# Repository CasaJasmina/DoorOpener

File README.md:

# Door Opener
A combination of a capacitive keypad/doorbell and a hacked lockitron.
At the moment there is a wired connection between the two parts of the project allowing the opening of the door when the right combination is pressed.

## The keypad

The keypad is based on Arduino YUN.
It uses MPR1221 for capacitive touch detection and addressable RGB led to provide feedbacks to the user.
find more inside the keypad folder

## The lockitron

To open the door a old model of lockitron was hacked. You can get the mechanical parts from Adafruit.
A custom PCB based on ESP8266 was designed and milled.

## TODO
- connect the system to Arduino Cloud

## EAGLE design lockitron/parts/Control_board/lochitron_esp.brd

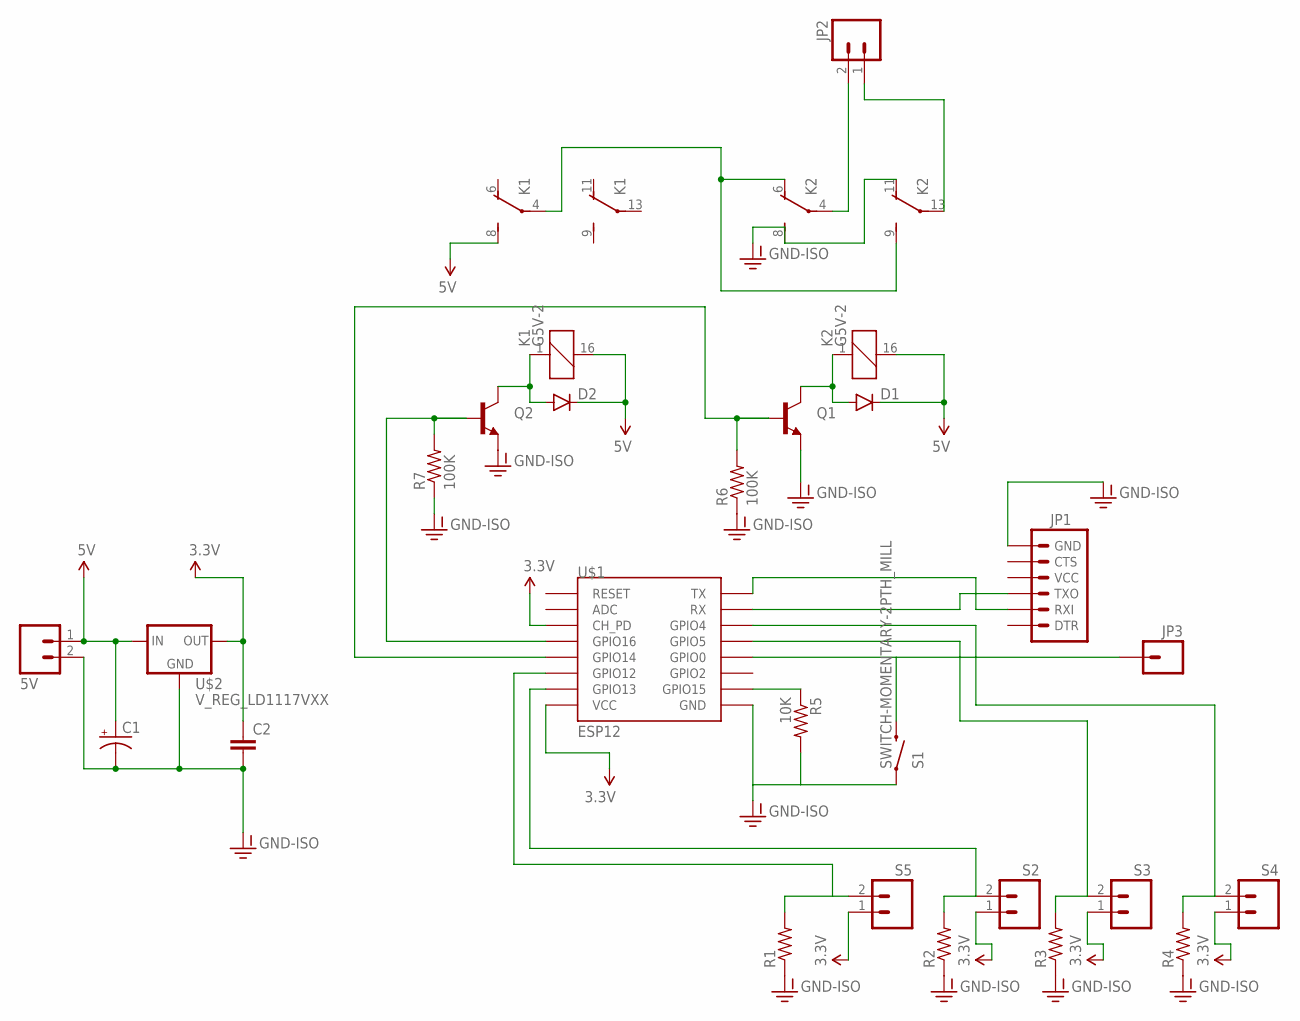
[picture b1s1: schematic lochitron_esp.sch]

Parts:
5V: M02LOCK_LONGPADS; 1X02_LOCK_LONGPADS
C1: 100UF-25V-20%(PTH); CPOL-RADIAL-100UF-25V
C2: 0.1UF-50V-20%(PTH)KIT-EZ; CAP-PTH-SMALL-KIT
D1, D2: DIODE1N4148; DIODE-1N4148
JP1: ARDUINO_SERIAL_PROGRAMLONGPADS; 1X06_LONGPADS
JP2: M02LOCK_LONGPADS; 1X02_LOCK_LONGPADS
JP3: M01PTH_LONGPAD; 1X01_LONGPAD
K1, K2: G5V-2
Q1, Q2: TRANSISTOR_NPNBC547; TO-92-AMMO
R1, R2, R3, R4: RESISTORAXIAL-0.3; AXIAL-0.3
R5: 10K; AXIAL-0.3
R6, R7: 100K; AXIAL-0.3
S1: SWITCH-MOMENTARY-2PTH_MILL; TACTILE-PTH
S2, S3, S4, S5: M02LOCK_LONGPADS; 1X02_LOCK_LONGPADS
U$1: ESP12
U$2: V_REG_LD1117VXX; 78XXL

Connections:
3.3V: C2.1, S2.1, S3.1, S4.1, S5.1, U$1.CH_PD, U$1.VCC, U$2.GND (OUT)
5V: 5V.1, C1.1 (+), D1.C, D2.C, K1.8 (S), K1.16 (2), K2.16 (2), U$2.OUT (IN)
GND-ISO: 5V.2, C1.2 (-), C2.2, JP1.6 (GND), K2.8 (S), K2.11 (O), Q1.3 (E), Q2.3 (E), R1.P$1 (1), R2.P$1 (1), R3.P$1 (1), R4.P$1 (1), R5.P$2 (2), R6.P$1 (1), R7.P$1 (1), S1.1, U$1.GND, U$2.IN (GND)
unnamed: D2.A, K1.1, Q2.1 (C)
unnamed: D1.A, K2.1, Q1.1 (C)
unnamed: JP3.1, S1.3 (2), U$1.GPIO0
unnamed: JP1.3 (TXO), U$1.RX
unnamed: JP1.2 (RXI), U$1.TX
unnamed: K1.4, K2.6 (O), K2.9 (S)
unnamed: R5.P$1 (1), U$1.GPIO15
unnamed: R2.P$2 (2), S2.2, U$1.GPIO13
unnamed: Q2.2 (B), R7.P$2 (2), U$1.GPIO16
unnamed: R4.P$2 (2), S4.2, U$1.GPIO4
unnamed: R3.P$2 (2), S3.2, U$1.GPIO5
unnamed: R1.P$2 (2), S5.2, U$1.GPIO12
unnamed: JP2.2, K2.4
unnamed: JP2.1, K2.13
unnamed: Q1.2 (B), R6.P$2 (2), U$1.GPIO14

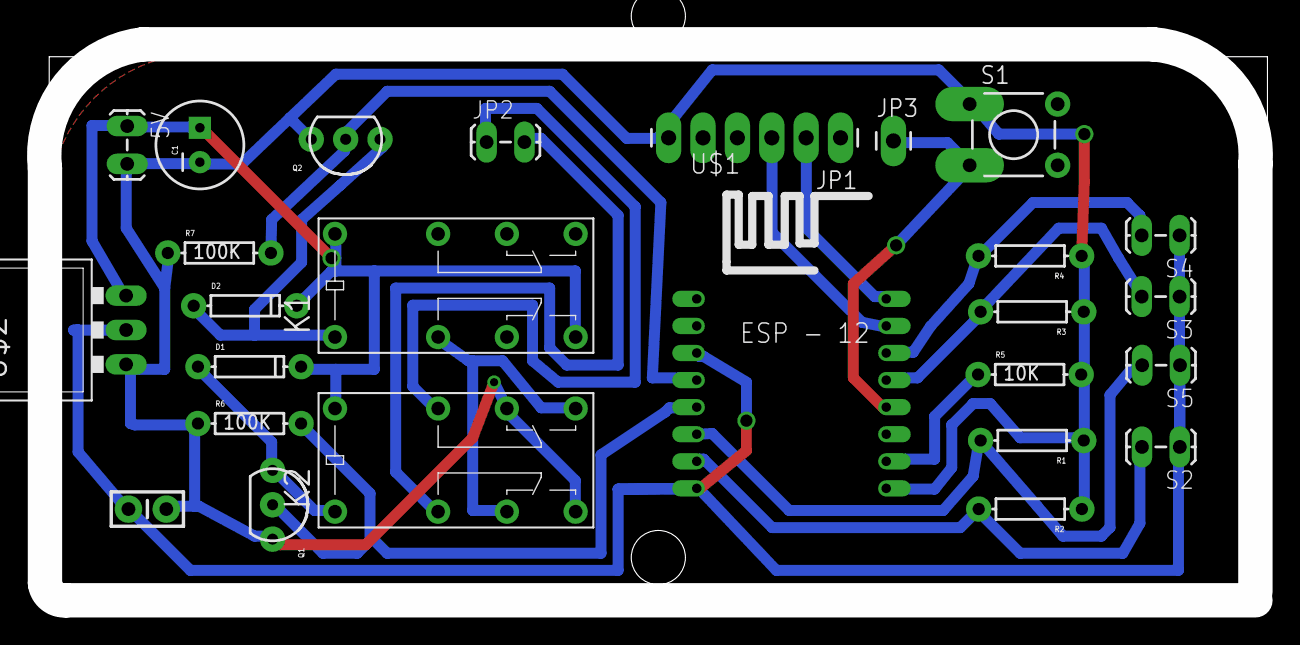
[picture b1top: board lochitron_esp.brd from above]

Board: 2 copper layers, 89.5 x 41.1 mm, 26 parts (0 on the bottom side), 18 nets.

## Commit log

2015-10-12 added pics
2015-10-12 added images in readme.MD

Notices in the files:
parts and their libraries:
SparkFun-Connectors: Licensing: Creative Commons ShareAlike 4.0 International - https://creativecommons.org/licenses/by-sa/4.0
